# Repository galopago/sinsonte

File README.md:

# SOUND PLAYER BASED ON RPI PICO

Sound player based on Raspberry Rpi Pico. Sound data are stored in onboard memory. Very few external (easy to find & solder) components required. The project was designed to be in sleep mode for a very long time powered by batteries. Can be used for musical wall clocks, talking dolls, toys, etc.

Printed circuit board with all components soldered.

Also read this in other languages: [Espanol](/docs/README.es.md)

## Working principle

The circuit ([see schematic](/docs/schematic.pdf)) has been designed to stay most of the time in silence powered by 2 AA batteries, like musical wall clocks or talking toys. In the best scenario, Rpi Pico in in deep sleep mode, will drain approx 1.3 mAh from the batteries. A pair of AA batteries in series have around 2000 mAh of juice, just in standby they will last only for two months. Unacceptable!.

An external circuit was added to totally power off Rpi Pico via 3V3_EN pin. Draining just only 70 uAh, which translates to 3 years of standby. Much better!

The circuit work in the following manner: In standby mode, a capacitor with a large resistor holds the conduction voltage of a MOSFET which is in charge of tying 3V3_EN to ground, powering off the board completely. To play a sound, click briefly on the push button which discharges the capacitor and stops conduction of the MOSFET. Now 3V3_EN pin is tied to V+ via its internal pull up, powering on the Rpi Pico Board. Once powered on and program booted, it keeps the capacitor discharged via a GPIO while sound is played. When the sound ends, the RPI Pico puts the GPIO in high impedance state, so the capacitor charges again and Rpi Powers off until the next click on the button!

There are many stored sounds in the Rpi Pico, and they are played in sequence. To know which sound needs to be played in the next click, some data needs to be preserved between power offs, that data is stored in the internal flash memory. Be careful modifying the program to keep flash writes to a minimum.

The program was written using the Rpi Pico SDK and more or less the same functionality also in CircuitPython too!

## Directory structure

Hardware folder contains schematic and printed circuit board.
* /hardware/ folder contains KiCad V5.1 project
* /hardware/gerber folder contains ready to manufacture files.
* /hardware/modules folder contains additional footprints needed to edit printed circuit board.
* /hardware/library folder contains additional symbols needed to edit schematic.

Software folder contains program source code.
* /software/sdk folder contains C source code for multiple apps develped with the Raspberry **Pi Pico SDK**.
* /software/sdk/clock/build folder will contain downloadable binaries once compiled.
* /software/sdk/_utils folder contain additional python scripts.
* /software/sdk/_uf2_binaries folder contains compiled programs ready for download to the Rpi Pico.
* /software/sdk/_sounds folder contains sound files source in form of C arrays[].

* /software/cp folder contains Python source code for multiple apps develped with **CircuitPython**.
* /software/cp/_sounds folder contains sound files source in .mp3 format
* /software/cp/_utils folder contains contains binary files

Docs folder contains additional info files

# C/C++ SDK
## How to use this repository

This is a very brief guide how to install Rpi Pico SDK on Linux (Ubuntu!). For more info please visit [official repo](https://github.com/raspberrypi/pico-sdk)
~~~
sudo apt install cmake gcc-arm-none-eabi libnewlib-arm-none-eabi build-essential
git clone -b master https://github.com/raspberrypi/pico-sdk.git
cd pico-sdk
git submodule update --init
~~~
Add the line below to .bashrc file, and then restart session to allow changes to take effect.
~~~
export PICO_SDK_PATH={sdk path}/pico-sdk
~~~
Clone project repository
~~~
git clone https://github.com/galopago/SINSONTE.git
~~~
* Modify /SINSONTE/software/sdk/clock/CMakeLists.txt file change Rpi Pico SDK paths with your own installation paths.
* Delete /SINSONTE/software/sdk/clock/build/CMakeCache.txt file
* Delete /SINSONTE/software/sdk/clock/build/elf2uf2/CMakeCache.txt file

Using the command line terminal go to the folder /SINSONTE/software/sdk/clock/build
~~~
cd software/sdk/clock/build
~~~
Generate makefiles
~~~
cmake ..
~~~
And finally compile:
~~~
make clean
make all
~~~
(.uf2) downloadable compiled file lies in /SINSONTE/software/sdk/clock/build

## How to change sound files

The sample program shown here, plays 12 different sound files sequentially. If you want to change one or all of them, the following rules must be taken into account:

* Max sound storage capacity is 24 seconds total (~2 seconds per file * 12 files = ~24 seconds)
* Sound files have to be in .WAV mono 16 bit @ 44100 hz before being processed by the script which converts them into C array[]

Look for **wav2c.py** script in /SINSONTE/software/sdk/_utils/ folder to convert your own sounds.

This script need two parameters: input sound file name (.wav) and output file name (.h). The files have to be named 1.h to 12.h. Here is an example:

~~~
python3 wav2c.py example.wav 5.h
~~~

The generated file (5.h) needs to be put in /SINSONTE/software/sdk/clock folder and then recompile!

# CircuitPython
## How to use this repository
Clone project repository
~~~
git clone https://github.com/galopago/SINSONTE.git
~~~
* Put Rpi Pico in programming mode and then plug into a PC
* To start fresh, download to the Rpi Pico the file **flash_nuke.uf2** located in /SINSONTE/software/cp/_utils
* Put Rpi Pico in programming mode again and then plug into a PC
* Install CircuitPython runtime downloading the file **adafruit-circuitpython-raspberry_pi_pico-en_US-6.3.0.uf2** located in /SINSONTE/software/cp/_utils
* Once CircuitPython is installed, download to the Rpi Pico **code.py** and the sound files (1.mp3 to 12.mp3) located in /SINSONTE/software/cp/clock folder

## How to change sound files
Download to the Rpi Pico your own .mp3 file, it needs to be named 1.mp3 to 12.mp3

## License
This is an Open Source project and is licensed under [MIT License](https://spdx.org/licenses/MIT.html)

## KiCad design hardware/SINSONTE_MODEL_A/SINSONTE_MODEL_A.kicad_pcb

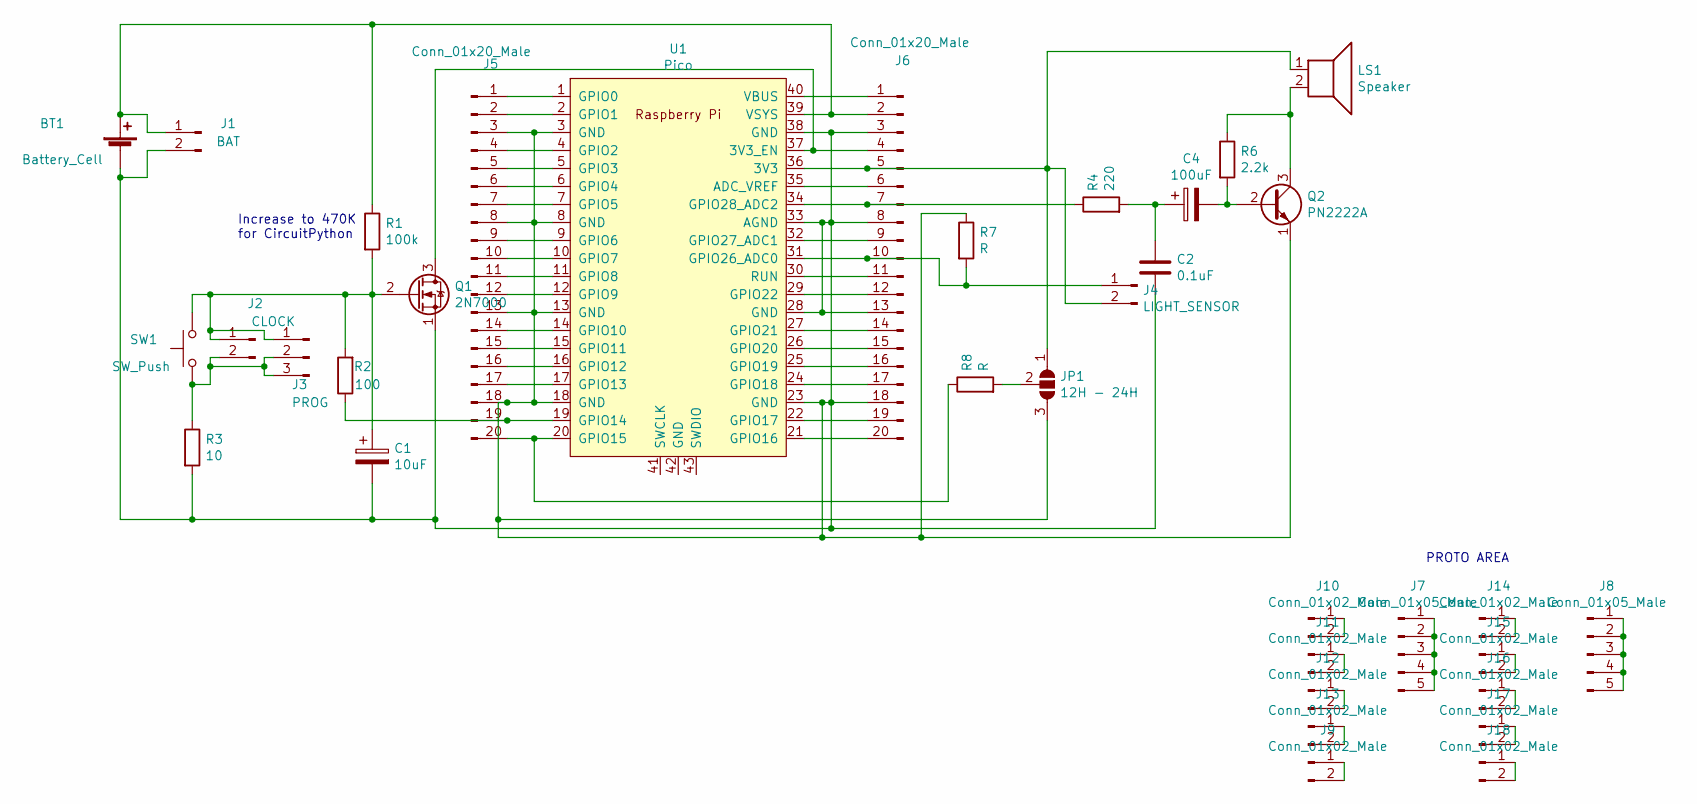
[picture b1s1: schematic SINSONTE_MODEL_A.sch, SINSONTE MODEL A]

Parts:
BT1: Battery_Cell; BatteryHolder_Keystone_2462_2xAA
C1: 10uF; CP_Radial_D6.3mm_P2.50mm
C2: 0.1uF; C_Disc_D5.0mm_W2.5mm_P5.00mm
C4: 100uF; CP_Radial_D6.3mm_P2.50mm
J1: BAT; TerminalBlock_4Ucon_1x02_P3.50mm_Horizontal
J2: CLOCK; PinHeader_1x02_P2.54mm_Vertical
J3: PROG; PinHeader_1x03_P2.54mm_Vertical
J4: LIGHT_SENSOR; PinHeader_1x02_P2.54mm_Vertical
J5, J6: Conn_01x20_Male; PinHeader_1x20_P2.54mm_Vertical
J7, J8: Conn_01x05_Male; PinHeader_1x05_P2.54mm_Vertical
J9, J10, J11, J12, J13, J14, J15, J16, J17, J18: Conn_01x02_Male; PinHeader_1x02_P2.54mm_Vertical
JP1: 12H - 24H; SolderJumper-3_P1.3mm_Open_RoundedPad1.0x1.5mm_NumberLabels
LS1: Speaker; PinHeader_1x02_P2.54mm_Vertical
Q1: 2N7000; TO-92_HandSolder
Q2: PN2222A; TO-92_HandSolder
R1: 100k; R_Axial_DIN0204_L3.6mm_D1.6mm_P2.54mm_Vertical
R2: 100; R_Axial_DIN0204_L3.6mm_D1.6mm_P2.54mm_Vertical
R3: 10; R_Axial_DIN0204_L3.6mm_D1.6mm_P2.54mm_Vertical
R4: 220; R_Axial_DIN0204_L3.6mm_D1.6mm_P2.54mm_Vertical
R6: 2.2k; R_Axial_DIN0204_L3.6mm_D1.6mm_P2.54mm_Vertical
R7, R8: R; R_Axial_DIN0204_L3.6mm_D1.6mm_P2.54mm_Vertical
SW1: SW_Push; SW_PUSH_6mm_H4.3mm
U1: Pico; RPi_Pico_SMD_TH

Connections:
unnamed: BT1.1 (+), J1.1, J6.2, R1.1, U1.39 (VSYS)
unnamed: BT1.2 (-), C1.2, C2.2, J1.2, J5.3, J5.8, J5.13, J5.18, J6.3, J6.8, J6.13, J6.18, JP1.3 (B), Q1.1 (S), Q2.1 (E), R3.2, R7.1, U1.3 (GND), U1.8 (GND), U1.13 (GND), U1.18 (GND), U1.23 (GND), U1.28 (GND), U1.33 (AGND), U1.38 (GND)
unnamed: C1.1, J2.1, J3.1, Q1.2 (G), R1.2, R2.2, SW1.1
unnamed: C2.1, C4.1, R4.2
unnamed: C4.2, Q2.2 (B), R6.2
unnamed: J2.2, J3.2, J3.3, R3.1, SW1.2
unnamed: J4.1, J6.10, R7.2, U1.31 (GPIO26_ADC0)
unnamed: J4.2, J6.5, JP1.1 (A), LS1.1, U1.36 (3V3)
unnamed: J5.1, U1.1 (GPIO0)
unnamed: J5.2, U1.2 (GPIO1)
unnamed: J5.4, U1.4 (GPIO2)
unnamed: J5.5, U1.5 (GPIO3)
unnamed: J5.6, U1.6 (GPIO4)
unnamed: J5.7, U1.7 (GPIO5)
unnamed: J5.9, U1.9 (GPIO6)
unnamed: J5.10, U1.10 (GPIO7)
unnamed: J5.11, U1.11 (GPIO8)
unnamed: J5.12, U1.12 (GPIO9)
unnamed: J5.14, U1.14 (GPIO10)
unnamed: J5.15, U1.15 (GPIO11)
unnamed: J5.16, U1.16 (GPIO12)
unnamed: J5.17, U1.17 (GPIO13)
unnamed: J5.19, R2.1, U1.19 (GPIO14)
unnamed: J5.20, R8.1, U1.20 (GPIO15)
unnamed: J6.1, U1.40 (VBUS)
unnamed: J6.4, Q1.3 (D), U1.37 (3V3_EN)
unnamed: J6.6, U1.35 (ADC_VREF)
unnamed: J6.7, R4.1, U1.34 (GPIO28_ADC2)
unnamed: J6.9, U1.32 (GPIO27_ADC1)
unnamed: J6.11, U1.30 (RUN)
unnamed: J6.12, U1.29 (GPIO22)
unnamed: J6.14, U1.27 (GPIO21)
unnamed: J6.15, U1.26 (GPIO20)
unnamed: J6.16, U1.25 (GPIO19)
unnamed: J6.17, U1.24 (GPIO18)
unnamed: J6.19, U1.22 (GPIO17)
unnamed: J6.20, U1.21 (GPIO16)
unnamed: J7.1, J7.2, J7.3, J7.4, J7.5
unnamed: J8.1, J8.2, J8.3, J8.4, J8.5
unnamed: J9.1, J9.2
unnamed: J10.1, J10.2
unnamed: J11.1, J11.2
unnamed: J12.1, J12.2
unnamed: J13.1, J13.2
unnamed: J14.1, J14.2
unnamed: J15.1, J15.2
unnamed: J16.1, J16.2
unnamed: J17.1, J17.2
unnamed: J18.1, J18.2
unnamed: JP1.2 (C), R8.2
unnamed: LS1.2, Q2.3 (C), R6.1

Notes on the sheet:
Increase to 470K for CircuitPython
PROTO AREA

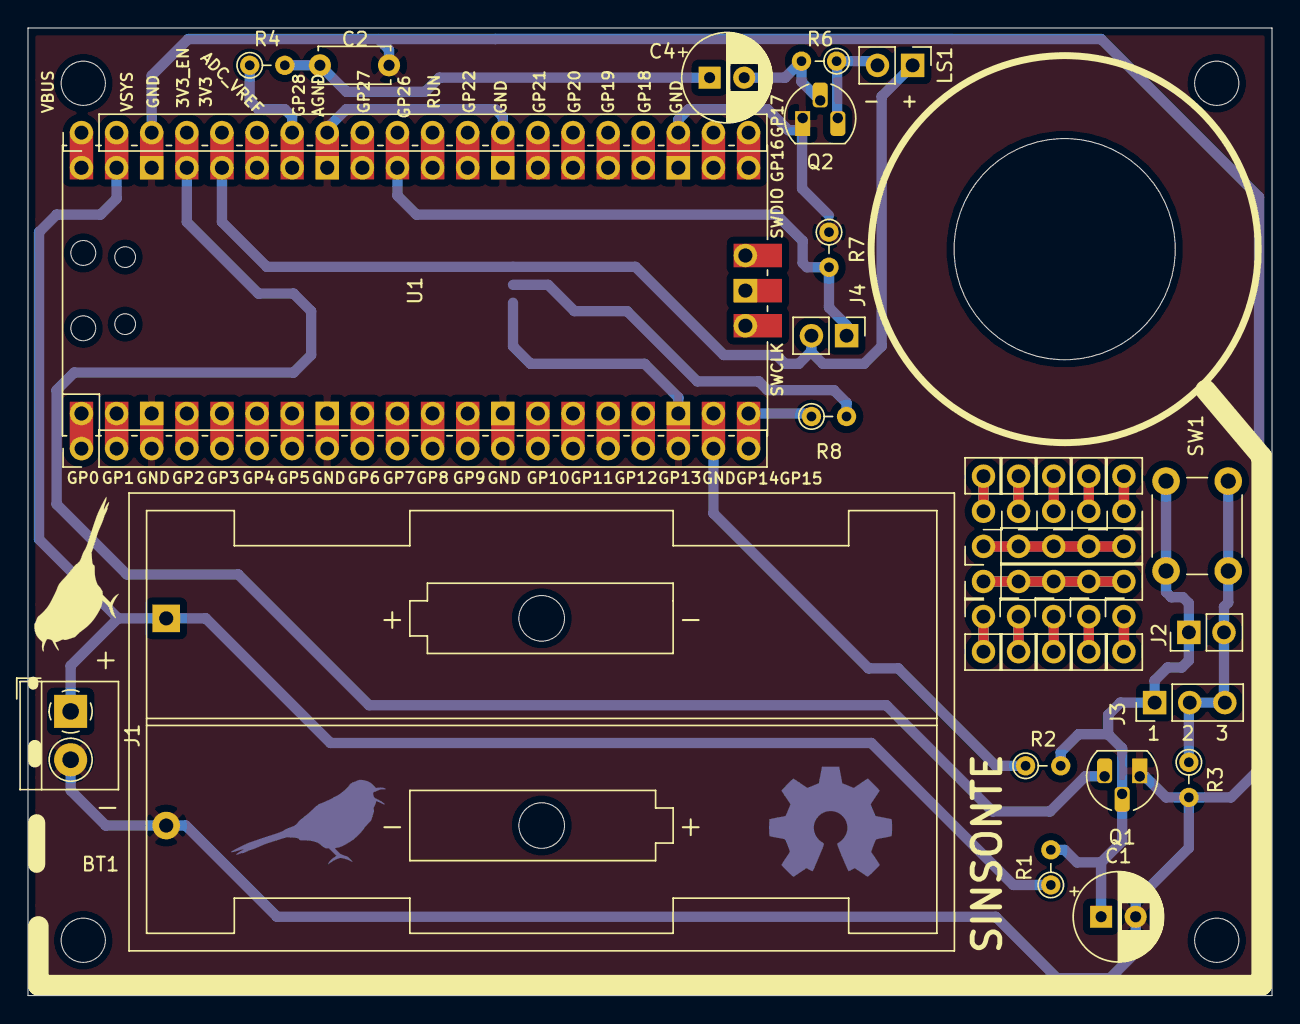
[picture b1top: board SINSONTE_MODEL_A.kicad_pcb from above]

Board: 2 copper layers, 90.0 x 70.0 mm, 35 parts (1 on the bottom side), 51 nets.

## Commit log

2021-03-08 created repo
2021-03-08 power on/off elements added
2021-03-08 core components added
2021-03-09 updated features elements added
2021-03-10 90% routed
2021-03-10 all traces routed
2021-03-11 sw project cleaned
2021-03-12 resistor removed
2021-03-13 expansion headers
2021-03-14 changed autopower off strategy
2021-03-14 mounting holes
2021-03-14 all expansion headers placed
2021-03-14 copper ground plane, need some checks
2021-03-15 changed transistors footprint for handsolder
2021-03-16 updated gerbers
2021-03-18 trace a bit away from edge
2021-03-18 program jumper trace minor update
2021-04-05 just 11 hour sound missing
2021-04-05 all 12 hour sounds added
2021-04-19 moved speaker a bit and cleaned some refs silks
2021-04-19 some pcb decorations
2021-04-20 top silks finished
2021-04-21 all silks finished
2021-04-22 gerbers generated
2021-04-22 some code retouches
2021-04-22 wav software first beta
2021-04-26 cu plane added front
2021-06-04 compontent values sch added
2021-06-04 capacitor fixed polarity
2021-08-15 changed light sensor resistor to pull-down
2021-08-15 updated gerbers light sensor
2021-08-16 light sensor code added
2021-10-11 added sound folder
2021-10-11 hint to build software
2021-10-11 debunging uart adc
2021-10-11 lux sensor data table added
2021-10-12 added external led output
2021-10-12 half halloween sounds
2021-10-12 8 hours hallowen
2021-10-12 halloween sounds finished
2021-10-12 uf2 binaries renamed
2021-10-12 halloween sounds by default
2021-10-12 moved python convert file to other folder
2021-10-13 initial hints to make repository compile
2021-10-13 changed files to folder
2021-10-13 some info added
2021-10-14 starting readme ES
2021-10-14 renamed folder
2021-10-14 first touches ES help
2021-10-14 more touches ES help
2021-10-14 more touches+ ES help
2021-10-14 more comments to source file
2021-10-14 more touches++ ES help
2021-10-14 more touches+++ ES help
2021-10-14 more touches++++ ES help
2021-10-14 more touches+++++ ES help
2021-10-14 more touches++++++ ES help
2021-10-14 repo ES help
2021-10-14 repo codeblock ES help
2021-10-14 repo codeblock + ES help
2021-10-14 repo+build ES help
2021-10-14 repo+build+ ES help
2021-10-14 repo+build+bug ES help
2021-10-15 wav to h example
2021-10-15 lowered light thr
2021-10-15 readme ES corrections
2021-10-15 readme ES corrections done
2021-10-15 readme EN started
2021-10-15 license
2021-10-15 Readme EN first paragraph
2021-10-15 Readme EN translating
2021-10-15 Readme EN translating+
2021-10-16 readme EN almost translated
2021-10-16 readme EN all translated
2021-10-16 readme EN correcting
2021-10-16 readme EN correcting+
2021-10-16 readme EN correcting++
2021-10-16 readme EN correcting+++
2021-10-16 readme EN correcting++++
2021-10-16 readme EN correcting+++++
2021-10-16 readme EN correcting++++++
2021-10-16 readme EN corrected
2021-10-16 added folder skd
2021-10-16 changes in readme EN
2021-10-16 cp first steps
2021-10-16 add note to change R1 for CP
2021-10-16 testing NVM function in CP
2021-10-17 hours in sequence working
2021-10-17 light sensor added
2021-10-17 ext led gpio10 added
2021-10-17 ext led gpio10 added sdk
2021-10-17 updated picture
2021-10-18 code working in SDK and CP
2021-10-18 Added CP instructions to Readme EN
2021-10-18 Added list
2021-10-18 SINSONTE folder desc
2021-10-18 C/C++ desc added
2021-10-18 bold
2021-10-18 readme ES corrections+
2021-10-18 readme ES corrected
2021-10-24 change folder structure to allow multiple apps
2021-10-24 changed readme folders structure
2021-10-24 CP random example
2021-10-25 updated readmes multiple project folders
2021-10-25 updated examples random
2021-11-09 changed ext batt for screw terminal type
2021-11-09 rpi first half conn aded 1 pos on ground
2021-11-09 rpi first half conn aded all pins connector
2021-11-09 rpi second half conn aded all pins connector
2021-11-10 added proto area
2021-11-10 minor adjustments
2021-11-10 gerber files generated
2021-11-10 created model A variant
2021-11-10 created model B variant
2021-11-10 deleted initial first project before variants
2021-11-10 shrinkikng in process
2021-11-10 shrinkikng finished
2021-11-10 single gerber
2021-11-10 single gerber proto fix
2021-11-10 panel gerber proto fix
2021-11-10 small gpio silk fix
